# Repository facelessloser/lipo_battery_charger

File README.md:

# lipo_battery_charger
A board I designed to link a lipo battery charger board with a DC-DC booster board. This allows me to charger and power my projects

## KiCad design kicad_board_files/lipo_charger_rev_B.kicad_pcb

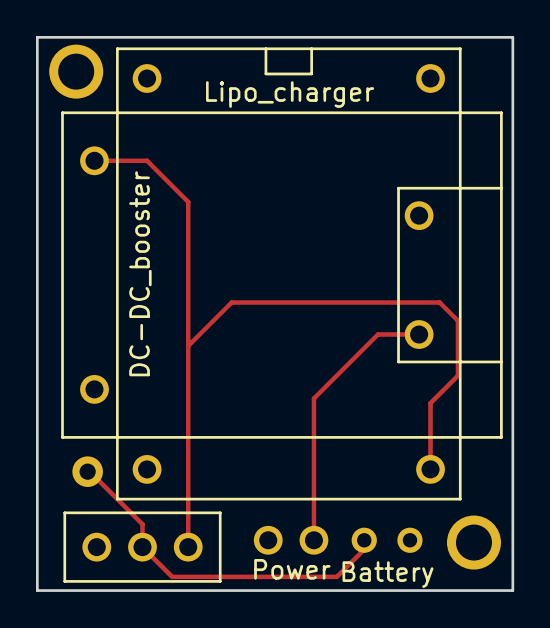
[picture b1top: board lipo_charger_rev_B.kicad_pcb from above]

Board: 2 copper layers, 26.4 x 30.7 mm, 9 parts (0 on the bottom side), 4 nets.

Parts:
1PIN, 1PIN#2: P***; 1pin
SW1: SWITCH_INV; Through_hole_switch_custom
U1: Lipo_charger; lipo_battery_charger
U2: DC-DC_booster
U3: Power; Power_connector
U4: BATTERY_MONITOR; battery_monitor
U5: Battery; new_battery_custom
VAL: OSH_final_silks_back

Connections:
GND: U1.1, U2.1, U2.3, U3.1, U5.1
unnamed: SW1.2, U4.1, U5.2
unnamed: U2.4, U3.2
VCC: SW1.1, U1.2, U2.2

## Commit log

2015-12-17 lipo battery charger gerbers rev_b
2016-09-24 Added board files
